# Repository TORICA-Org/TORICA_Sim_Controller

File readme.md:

# Software_Sim

Sim用のソフトウェア．  
ロードセルとHX711を使用して荷重を測定し重心位置を計算する．

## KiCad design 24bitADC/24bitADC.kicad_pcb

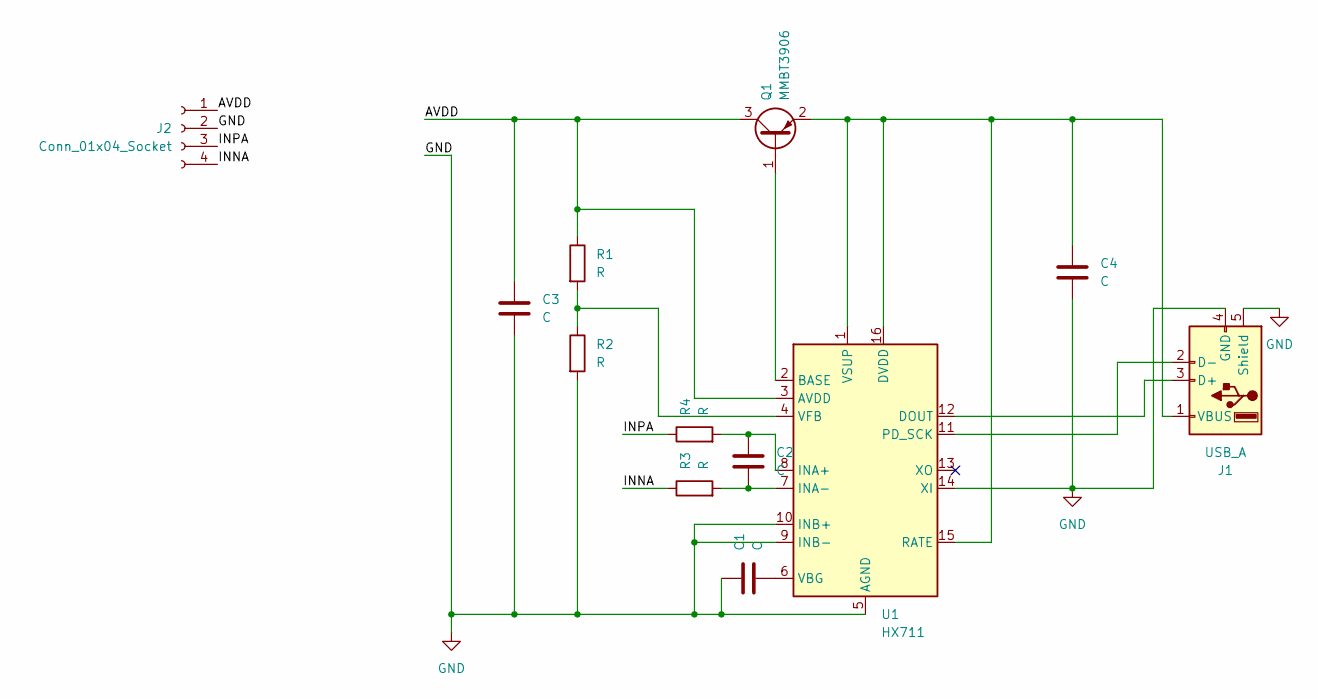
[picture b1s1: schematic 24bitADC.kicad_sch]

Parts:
C1, C2: C; C_0201_0603Metric_Pad0.64x0.40mm_HandSolder
C3, C4: C; C_0402_1005Metric_Pad0.74x0.62mm_HandSolder
J1: USB_A; USB_A_4P_Female
J2: Conn_01x04_Socket; 24bitADC_CN2_CN3
Q1: MMBT3906; SOT-23
R1, R2, R3, R4: R; R_0603_1608Metric_Pad0.98x0.95mm_HandSolder
U1: HX711; SOIC-16_3.9x9.9mm_P1.27mm

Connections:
/AVDD: C3.1, J2.1, Q1.3 (C), R1.1, U1.3 (AVDD)
/INNA: J2.4, R3.1
/INPA: J2.3, R4.1
GND: C1.1, C3.2, C4.2, J1.4 (GND), J1.5 (Shield), J2.2, R2.2, U1.5 (AGND), U1.9 (INB-), U1.10 (INB+), U1.14 (XI)
unnamed: J1.3 (D+), U1.12 (DOUT)
unnamed: J1.2 (D-), U1.11 (PD_SCK)
unnamed: C4.1, J1.1 (VBUS), Q1.2 (E), U1.1 (VSUP), U1.15 (RATE), U1.16 (DVDD)
unnamed: Q1.1 (B), U1.2 (BASE)
unnamed: C2.1, R4.2, U1.8 (INA+)
unnamed: C2.2, R3.2, U1.7 (INA-)
unnamed: C1.2, U1.6 (VBG)
unnamed: R1.2, R2.1, U1.4 (VFB)

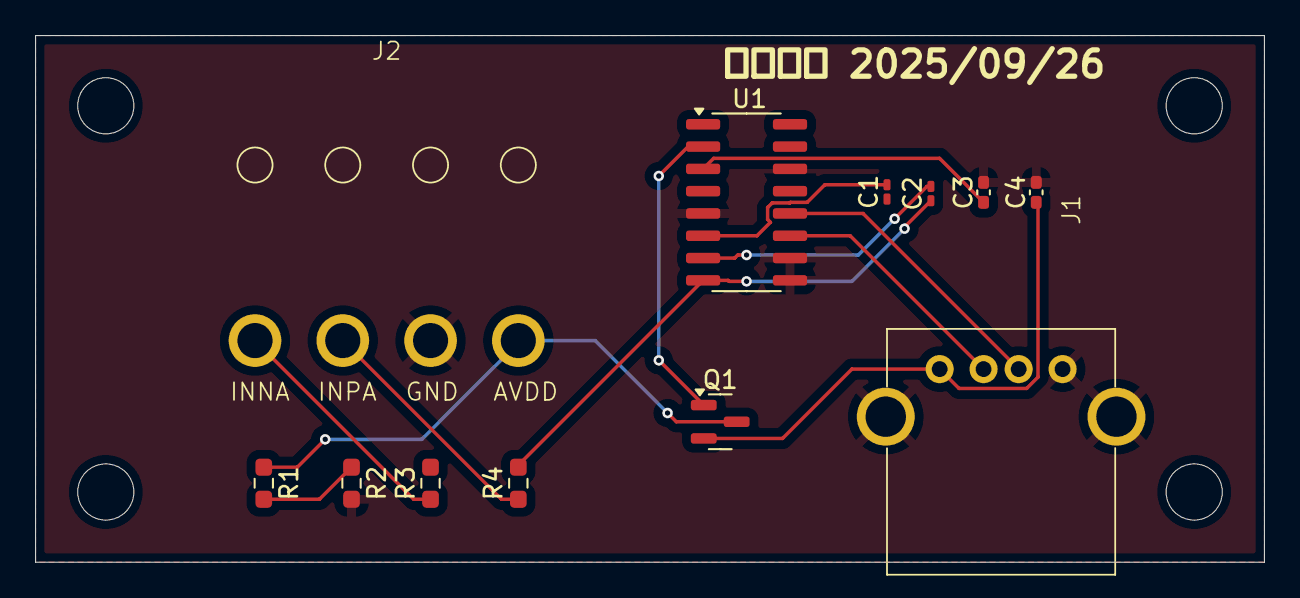
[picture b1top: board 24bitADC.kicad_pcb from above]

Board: 2 copper layers, 70.0 x 30.0 mm, 12 parts (0 on the bottom side), 12 nets.

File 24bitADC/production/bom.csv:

Designator,Footprint,Quantity,Value,LCSC Part #
"C1, C2",0201,2,C,
"C3, C4",0402,2,C,
J1,USB_A_4P_Female,1,USB_A,
J2,24bitADC_CN2_CN3,1,Conn_01x04_Socket,
Q1,SOT-23,1,MMBT3906,
"R1, R2, R3, R4",0603,4,R,
U1,SOIC-16_3.9x9.9mm_P1.27mm,1,HX711,

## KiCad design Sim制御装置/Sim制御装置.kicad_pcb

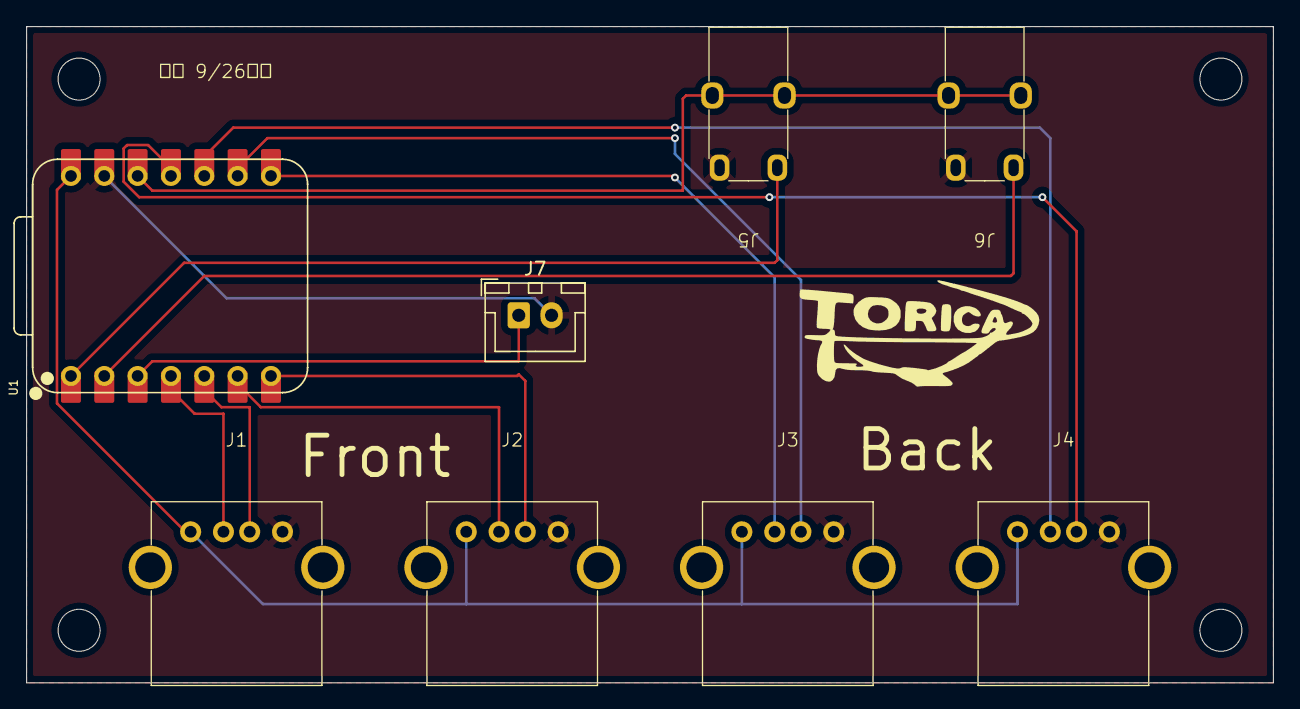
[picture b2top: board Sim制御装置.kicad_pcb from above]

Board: 2 copper layers, 95.0 x 50.0 mm, 8 parts (0 on the bottom side), 14 nets.

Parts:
J1, J2, J3, J4: USB_A; USB_A_4P_Female
J5, J6: AudioJack3; Audio_Jack_3P
J7: Conn_01x02_Socket; JST_XH_B2B-XH-A_1x02_P2.50mm_Vertical
U1: SeeeduinoXIAO; XIAO-RP2040-DIP

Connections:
/3V3: J5.T, J6.T, U1.12 (3V3)
/DOUT_1: J1.3 (D+), U1.5 (PA8_A4_D4_SDA)
/DOUT_2: J2.3 (D+), U1.7 (PB08_A6_D6_TX)
/DOUT_3: J3.3 (D+), U1.9 (PA7_A8_D8_SCK)
/DOUT_4: J4.3 (D+), U1.11 (PA6_A10_D10_MOSI)
/GND: J1.4 (GND), J2.4 (GND), J3.4 (GND), J4.4 (GND), J5.S, J6.S, J7.2, U1.13 (GND)
/SLK_1: J1.2 (D-), U1.4 (PA11_A3_D3)
/SLK_2: J2.2 (D-), U1.6 (PA9_A5_D5_SCL)
/SLK_3: J3.2 (D-), U1.8 (PB09_A7_D7_RX)
/SLK_4: J4.2 (D-), U1.10 (PA5_A9_D9_MISO)
/VDD: J1.1 (VBUS), J2.1 (VBUS), J3.1 (VBUS), J4.1 (VBUS), U1.14 (5V)
unnamed: J7.1, U1.3 (PA10_A2_D2)
unnamed: J5.R, U1.1 (PA02_A0_D0)
unnamed: J6.R, U1.2 (PA4_A1_D1)

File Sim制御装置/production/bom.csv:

Designator,Footprint,Quantity,Value,LCSC Part #
"J1, J2, J3, J4",USB_A_4P_Female,4,USB_A,
"J5, J6",Audio_Jack_3P,2,AudioJack3,
J7,JST_XH_B2B-XH-A_1x02_P2.50mm_Vertical,1,Conn_01x02_Socket,
U1,XIAO-RP2040-DIP,1,SeeeduinoXIAO,

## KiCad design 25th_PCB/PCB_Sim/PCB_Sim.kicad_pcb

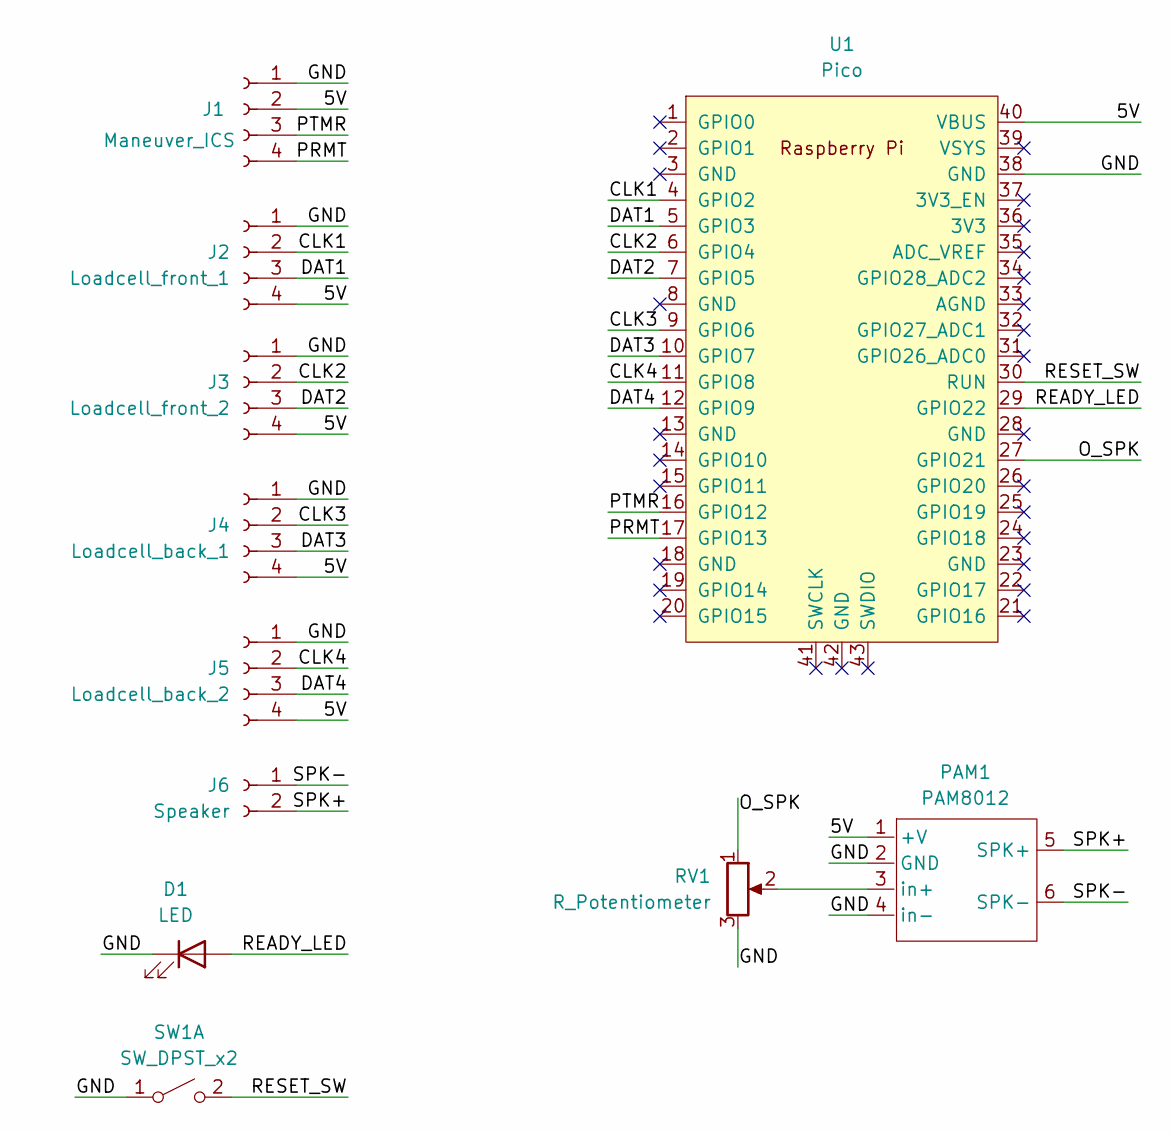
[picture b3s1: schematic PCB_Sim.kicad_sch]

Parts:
D1: LED; Padx2
J1: Maneuver_ICS; JST_XH_S4B-XH-A_1x04_P2.50mm_Horizontal
J2: Loadcell_front_1; JST_XH_S4B-XH-A_1x04_P2.50mm_Horizontal
J3: Loadcell_front_2; JST_XH_S4B-XH-A_1x04_P2.50mm_Horizontal
J4: Loadcell_back_1; JST_XH_S4B-XH-A_1x04_P2.50mm_Horizontal
J5: Loadcell_back_2; JST_XH_S4B-XH-A_1x04_P2.50mm_Horizontal
J6: Speaker; JST_XH_S2B-XH-A_1x02_P2.50mm_Horizontal
PAM1: PAM8012
RV1: R_Potentiometer; Padx3
SW1: SW_DPST_x2; Padx2
U1: Pico; RPi_Pico_SMD_TH

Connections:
/5V: J1.2, J2.4, J3.4, J4.4, J5.4, PAM1.1 (+V), U1.40 (VBUS)
/CLK1: J2.2, U1.4 (GPIO2)
/CLK2: J3.2, U1.6 (GPIO4)
/CLK3: J4.2, U1.9 (GPIO6)
/CLK4: J5.2, U1.11 (GPIO8)
/DAT1: J2.3, U1.5 (GPIO3)
/DAT2: J3.3, U1.7 (GPIO5)
/DAT3: J4.3, U1.10 (GPIO7)
/DAT4: J5.3, U1.12 (GPIO9)
/GND: D1.1 (K), J1.1, J2.1, J3.1, J4.1, J5.1, PAM1.2 (GND), PAM1.4 (in-), RV1.3, SW1.1 (A), U1.38 (GND)
/O_SPK: RV1.1, U1.27 (GPIO21)
/PRMT: J1.4, U1.17 (GPIO13)
/PTMR: J1.3, U1.16 (GPIO12)
/READY_LED: D1.2 (A), U1.29 (GPIO22)
/RESET_SW: SW1.2 (B), U1.30 (RUN)
/SPK+: J6.2, PAM1.5 (SPK+)
/SPK-: J6.1, PAM1.6 (SPK-)
unnamed: PAM1.3 (in+), RV1.2

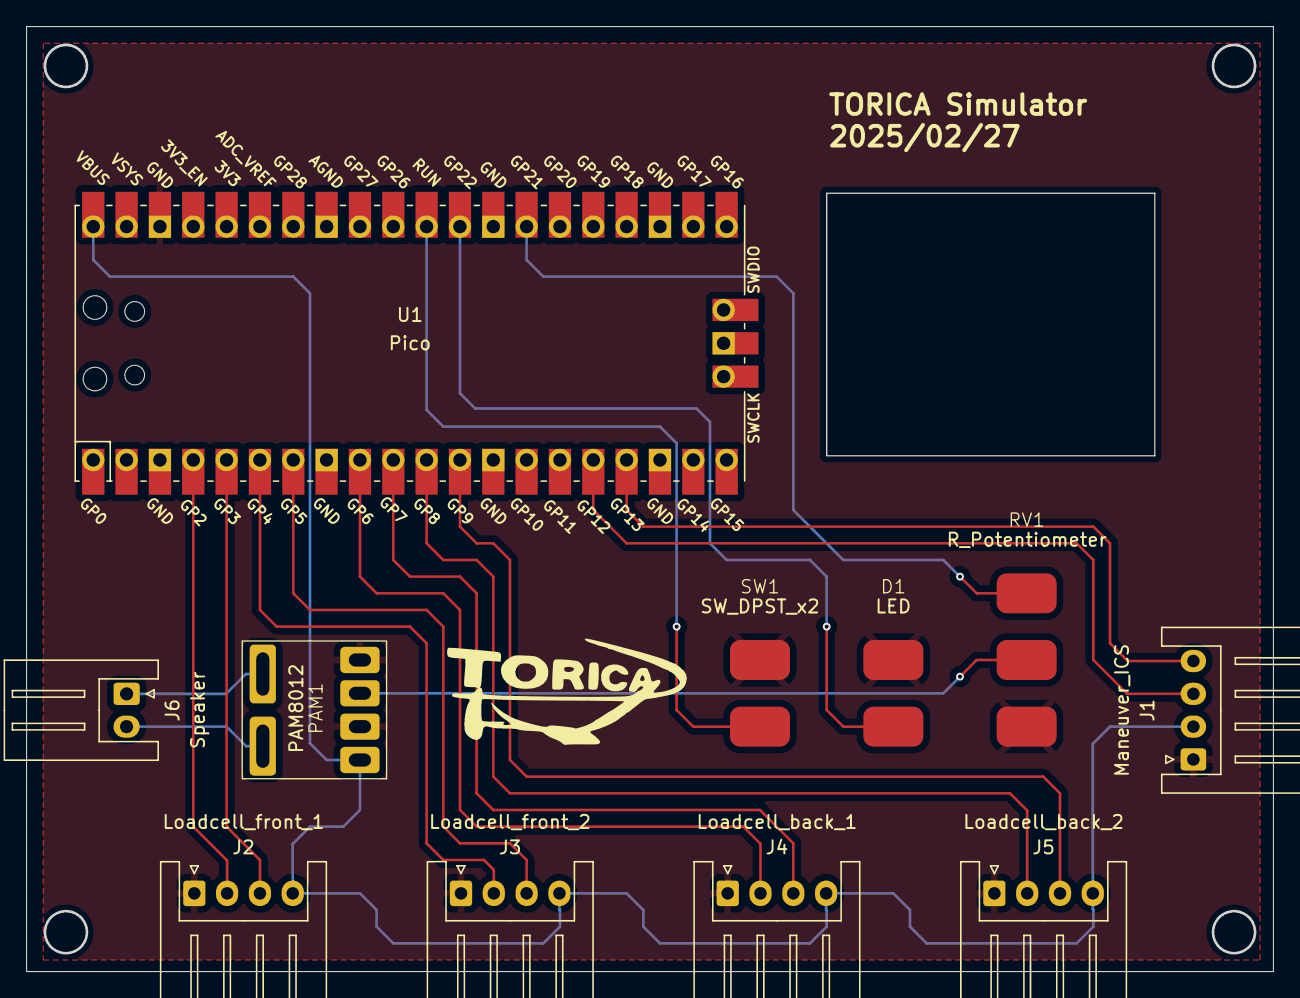
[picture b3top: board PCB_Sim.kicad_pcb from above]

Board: 2 copper layers, 95.0 x 72.0 mm, 11 parts (0 on the bottom side), 18 nets.

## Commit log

2025-02-14 Revive
    いろいろ再始動
2025-02-14 Save
2025-02-14 add note
2025-02-27 commit with browser
2025-02-27 first commit with browser
    ブラウザからのコミット
2025-02-27 ver.2
2025-02-27 Modify PCB
    軽微な修正
2025-02-27 Create PCB_HX711
    HX711用取り付け基盤
2025-02-28 Modify PCB_HX711
    タッピングの位置を離した
2025-03-02 Modify Software_Sim.ino
2025-03-03 Direct commit test
2025-03-04 Modify Software_Sim.ino
    ソフトウェア完成(^^)
2025-03-21 its a test
2025-03-21 via browser
2025-03-29 separated
2025-03-31 Maneuver
2025-04-14 organaized
2025-04-15 READY_LED set. ICS cannot work.
2025-04-17 offsetが反映されるように修正
2025-04-23 resetting issue has been resolved
2025-05-06 change rudder angle
2025-05-06 ニュートラル調整用可変抵抗省略版追加
2025-05-15 max and min set
2025-05-15 create .._constZero_..
2025-05-15 deleted some files
2025-05-15 directory is wrong
2025-05-15 overload
2025-05-15 default argument
2025-05-17 create RudderCalculator
2025-05-22 スピーカプログラム参考用
2025-05-22 スピーカー参考用
2025-05-22 スピーカ
2025-05-22 newfile
2025-05-22 スピーカ参考用1
2025-08-14 25th
2025-09-22 回路図作成
2025-09-23 Switch D- D+
2025-09-26 Sim制御装置の基盤データです。
2025-09-26 基盤作成
